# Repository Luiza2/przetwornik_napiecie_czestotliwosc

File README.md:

# przetwornik_napiecie_czestotliwosc
Projekt na przedmiot Metody Projektowania i Technika Realizacji

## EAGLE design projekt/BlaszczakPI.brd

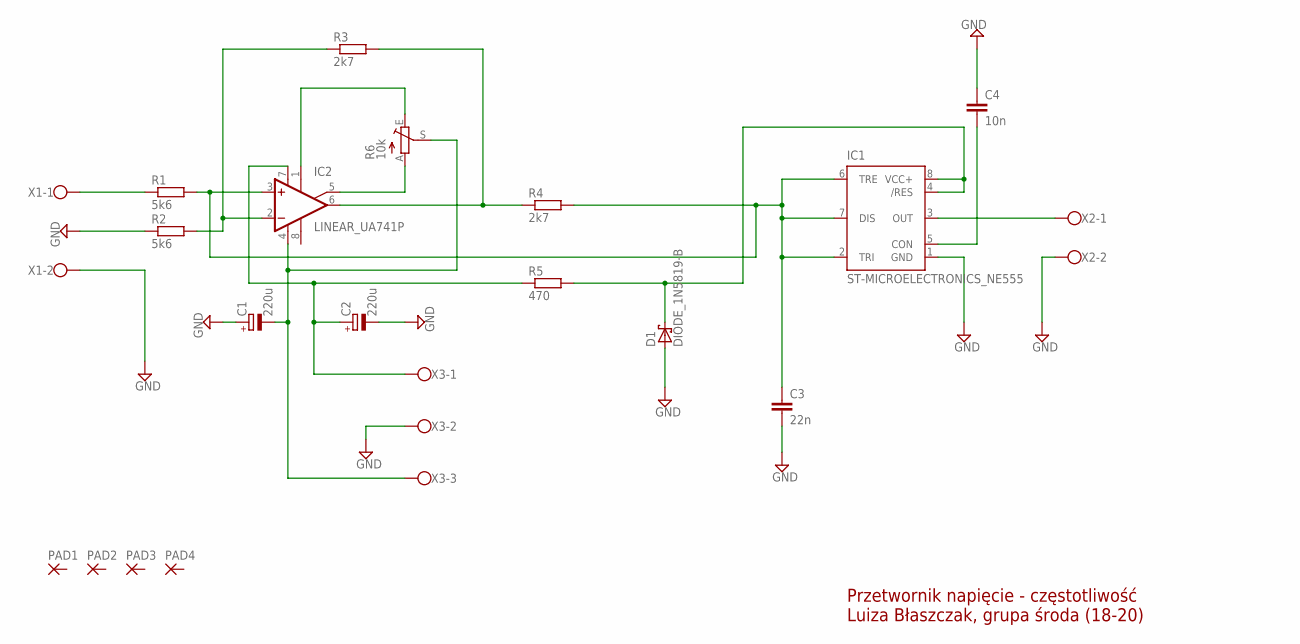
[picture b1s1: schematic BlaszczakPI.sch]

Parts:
C1, C2: 220u; RCL_E2,5-7
C3: 22n; C1206
C4: 10n; C1206
D1: DIODE_1N5819-B; DIODE_DO41-7.6
IC1: ST-MICROELECTRONICS_NE555; ST-MICROELECTRONICS_DIL-08
IC2: LINEAR_UA741P; LINEAR_DIL08
PAD1, PAD2, PAD3, PAD4: 2,54/1,1
R1, R2: 5k6; M1206
R3, R4: 2k7; M1206
R5: 470; M1206
R6: 10k; POT_CA6V
X1, X2: CON-WAGO-500_W237-102
X3: CON-WAGO-500_W237-103

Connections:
GND: C1.+, C2.-, C3.2, C4.1, D1.A, IC1.1 (GND), R2.1, X1.2, X2.2, X3.2
unnamed: R1.1, X1.1
unnamed: IC2.2 (-IN), R2.2, R3.1
unnamed: C1.-, IC2.4 (V-), R6.S, X3.3
unnamed: C2.+, IC2.7 (V+), R5.1, X3.1
unnamed: IC2.1 (ON1), R6.E
unnamed: IC2.5 (ON2), R6.A
unnamed: IC2.6 (OUT), R3.2, R4.1
unnamed: D1.C, IC1.4 (/RES), IC1.8 (VCC+), R5.2
unnamed: C4.2, IC1.5 (CON)
unnamed: IC1.3 (OUT), X2.1
R80: C3.1, IC1.2 (TRI), IC1.6 (TRE), IC1.7 (DIS), IC2.3 (+IN), R1.2, R4.2

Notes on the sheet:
Przetwornik napięcie - częstotliwość Luiza Błaszczak, grupa środa (18-20)

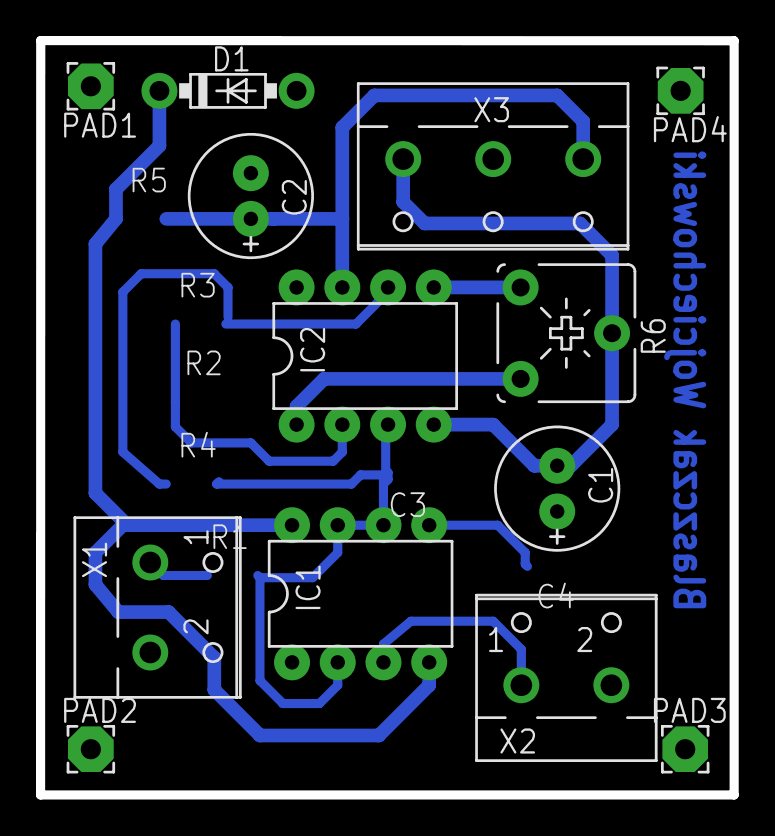
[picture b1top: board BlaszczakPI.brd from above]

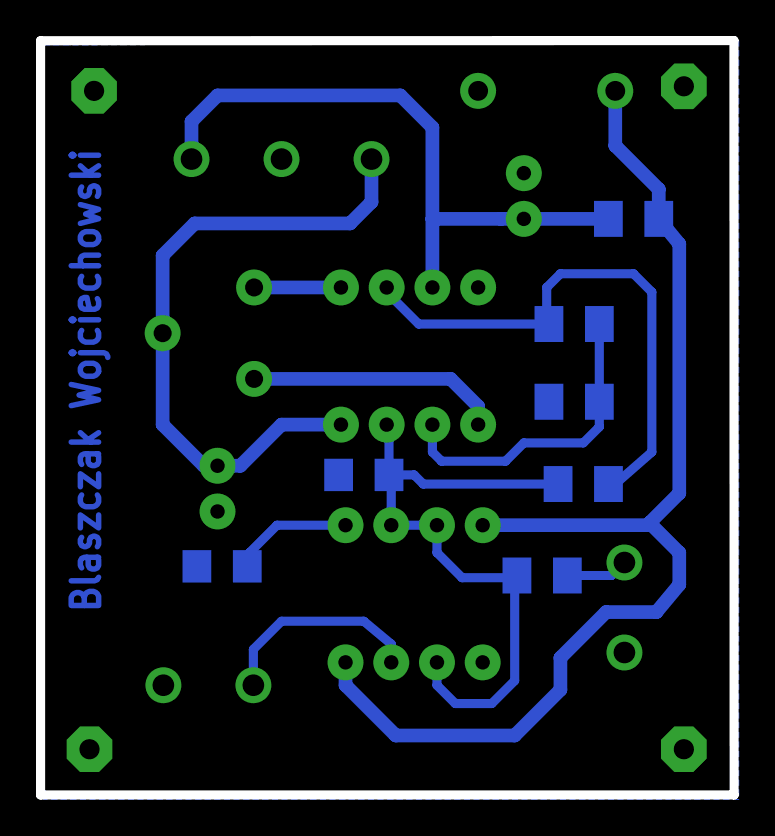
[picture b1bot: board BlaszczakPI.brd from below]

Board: 2 copper layers, 38.5 x 41.9 mm, 20 parts (7 on the bottom side), 12 nets.
